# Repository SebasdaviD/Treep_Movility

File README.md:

# Treep_Movility
Por Sebastian David Mazo Cadavid (sebastiandavidmazo@gmail.com) 

Repositorio para el código correspondiente a el desarrollo de la programación de los diferentes sistemas electrónicos de una moto eléctrica.

////////////////////////////                          Etapa de sensórica:                           /////////////////////////////////////////////////

La finalidad de esta etapa es describir de forma dínamica el comportamiento de la moto eléctrica, por lo que se van a medir las siguientes variables:

- Aceleraciones
- Giros
- Campo magnético
- Voltaje
- Corriente
- Potencia de electrónica
- Desplazamientos
- Ubicación global
- Velocidad angular

Para medir dichas variables se hace uso de la siguiente lista de dispositivos:

- Tarjeta de desarrollo WIDORA AIR V6.0

- Sensor MPU-9255 (DOF-IMU) 
    Medición de aceleraciones giros y campos magnéticos
    
- Multiplexor TCA9548A
    Usado para conectar varios dispositivos MPU-9255 de manera simultanea

- Módulo sensor de Efecto Hall 3144 5v
    Medición de velocidad
    
- Módulo de distancia Adafruit VL53L0X
    Usado para medir la distancia de desplazamiento de los amortiguadores

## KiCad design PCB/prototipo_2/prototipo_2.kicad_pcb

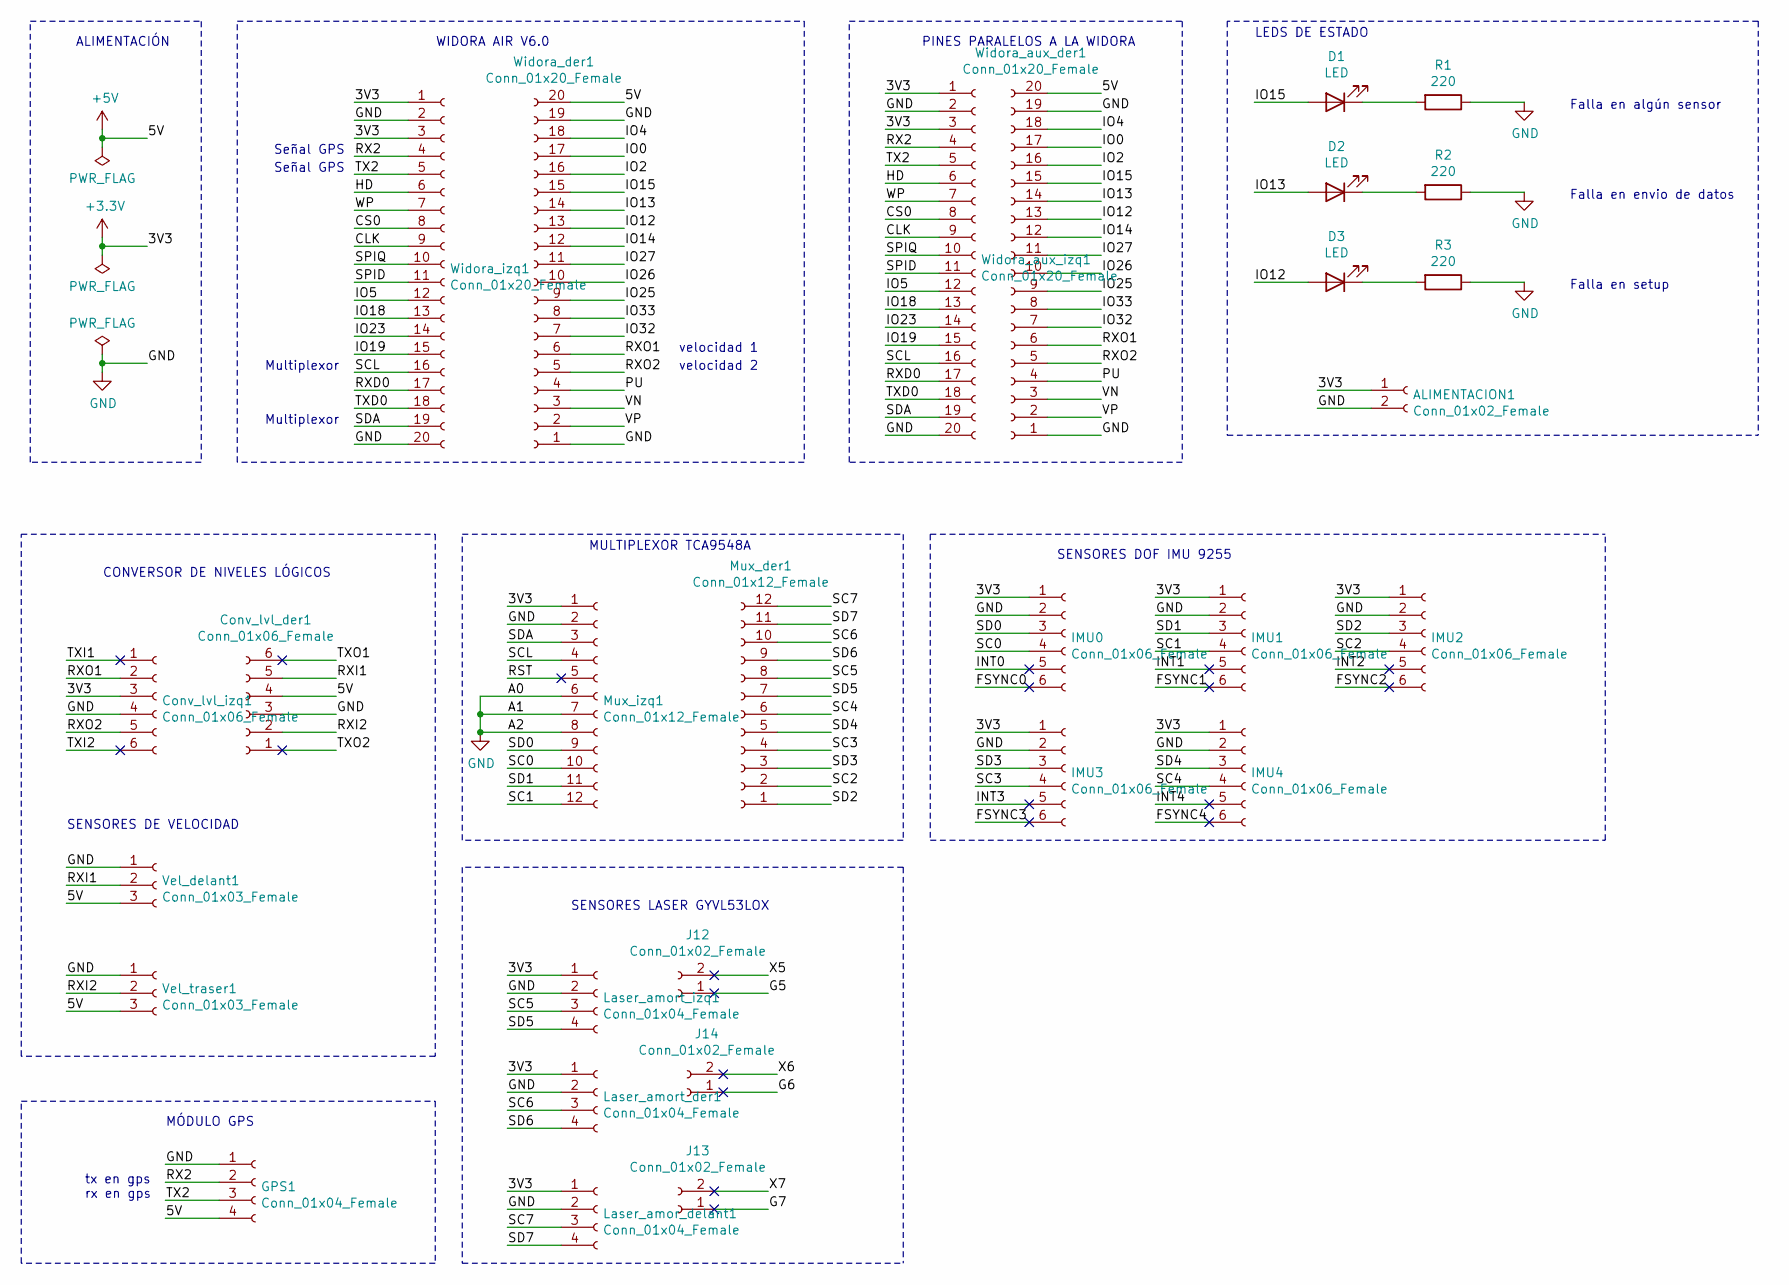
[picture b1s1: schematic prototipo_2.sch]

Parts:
ALIMENTACION1: Conn_01x02_Female; PinSocket_1x02_P2.54mm_Vertical
Conv_lvl_der1: Conn_01x06_Female; PinSocket_1x06_P2.54mm_Vertical
Conv_lvl_izq1: Conn_01x06_Female; PinSocket_1x06_P2.54mm_Vertical
D1, D2, D3: LED; LED_D5.0mm
GPS1: Conn_01x04_Female; PinSocket_1x04_P2.54mm_Vertical
IMU0, IMU1, IMU2, IMU3, IMU4: Conn_01x06_Female; PinSocket_1x06_P2.54mm_Vertical
J12, J13, J14: Conn_01x02_Female; PinSocket_1x02_P2.54mm_Vertical
Laser_amor_delant1: Conn_01x04_Female; PinSocket_1x04_P2.54mm_Vertical
Laser_amort_der1: Conn_01x04_Female; PinSocket_1x04_P2.54mm_Vertical
Laser_amort_izq1: Conn_01x04_Female; PinSocket_1x04_P2.54mm_Vertical
Mux_der1: Conn_01x12_Female; PinSocket_1x12_P2.54mm_Vertical
Mux_izq1: Conn_01x12_Female; PinSocket_1x12_P2.54mm_Vertical
R1, R2, R3: 220; R_Axial_DIN0411_L9.9mm_D3.6mm_P12.70mm_Horizontal
Vel_delant1: Conn_01x03_Female; PinSocket_1x03_P2.54mm_Vertical
Vel_traser1: Conn_01x03_Female; PinSocket_1x03_P2.54mm_Vertical
Widora_aux_der1: Conn_01x20_Female; PinSocket_1x20_P2.54mm_Vertical
Widora_aux_izq1: Conn_01x20_Female; PinSocket_1x20_P2.54mm_Vertical
Widora_der1: Conn_01x20_Female; PinSocket_1x20_P2.54mm_Vertical
Widora_izq1: Conn_01x20_Female; PinSocket_1x20_P2.54mm_Vertical

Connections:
+3V3: ALIMENTACION1.1, Conv_lvl_izq1.3, IMU0.1, IMU1.1, IMU2.1, IMU3.1, IMU4.1, Laser_amor_delant1.1, Laser_amort_der1.1, Laser_amort_izq1.1, Mux_izq1.1, Widora_aux_izq1.1, Widora_aux_izq1.3, Widora_izq1.1, Widora_izq1.3
+5V: Conv_lvl_der1.4, GPS1.4, Vel_delant1.3, Vel_traser1.3, Widora_aux_der1.20, Widora_der1.20
/CLK: Widora_aux_izq1.9, Widora_izq1.9
/CS0: Widora_aux_izq1.8, Widora_izq1.8
/FSYNC0: IMU0.6
/FSYNC1: IMU1.6
/FSYNC2: IMU2.6
/FSYNC3: IMU3.6
/FSYNC4: IMU4.6
/G5: J12.1
/G6: J14.1
/G7: J13.1
/HD: Widora_aux_izq1.6, Widora_izq1.6
/INT0: IMU0.5
/INT1: IMU1.5
/INT2: IMU2.5
/INT3: IMU3.5
/INT4: IMU4.5
/IO0: Widora_aux_der1.17, Widora_der1.17
/IO2: Widora_aux_der1.16, Widora_der1.16
/IO4: Widora_aux_der1.18, Widora_der1.18
/IO5: Widora_aux_izq1.12, Widora_izq1.12
/IO12: D3.2 (A), Widora_aux_der1.13, Widora_der1.13
/IO13: D2.2 (A), Widora_aux_der1.14, Widora_der1.14
/IO14: Widora_aux_der1.12, Widora_der1.12
/IO15: D1.2 (A), Widora_aux_der1.15, Widora_der1.15
/IO18: Widora_aux_izq1.13, Widora_izq1.13
/IO19: Widora_aux_izq1.15, Widora_izq1.15
/IO23: Widora_aux_izq1.14, Widora_izq1.14
/IO25: Widora_aux_der1.9, Widora_der1.9
/IO26: Widora_aux_der1.10, Widora_der1.10
/IO27: Widora_aux_der1.11, Widora_der1.11
/IO32: Widora_aux_der1.7, Widora_der1.7
/IO33: Widora_aux_der1.8, Widora_der1.8
/PU: Widora_aux_der1.4, Widora_der1.4
/RST: Mux_izq1.5
/RX2: GPS1.2, Widora_aux_izq1.4, Widora_izq1.4
/RXD0: Widora_aux_izq1.17, Widora_izq1.17
/RXI1: Conv_lvl_der1.5, Vel_delant1.2
/RXI2: Conv_lvl_der1.2, Vel_traser1.2
/RXO1: Conv_lvl_izq1.2, Widora_aux_der1.6, Widora_der1.6
/RXO2: Conv_lvl_izq1.5, Widora_aux_der1.5, Widora_der1.5
/SC0: IMU0.4, Mux_izq1.10
/SC1: IMU1.4, Mux_izq1.12
/SC2: IMU2.4, Mux_der1.2
/SC3: IMU3.4, Mux_der1.4
/SC4: IMU4.4, Mux_der1.6
/SC5: Laser_amort_izq1.3, Mux_der1.8
/SC6: Laser_amort_der1.3, Mux_der1.10
/SC7: Laser_amor_delant1.3, Mux_der1.12
/SCL: Mux_izq1.4, Widora_aux_izq1.16, Widora_izq1.16
/SD0: IMU0.3, Mux_izq1.9
/SD1: IMU1.3, Mux_izq1.11
/SD2: IMU2.3, Mux_der1.1
/SD3: IMU3.3, Mux_der1.3
/SD4: IMU4.3, Mux_der1.5
/SD5: Laser_amort_izq1.4, Mux_der1.7
/SD6: Laser_amort_der1.4, Mux_der1.9
/SD7: Laser_amor_delant1.4, Mux_der1.11
/SDA: Mux_izq1.3, Widora_aux_izq1.19, Widora_izq1.19
/SPID: Widora_aux_izq1.11, Widora_izq1.11
/SPIQ: Widora_aux_izq1.10, Widora_izq1.10
/TX2: GPS1.3, Widora_aux_izq1.5, Widora_izq1.5
/TXD0: Widora_aux_izq1.18, Widora_izq1.18
/TXI1: Conv_lvl_izq1.1
/TXI2: Conv_lvl_izq1.6
/TXO1: Conv_lvl_der1.6
/TXO2: Conv_lvl_der1.1
/VN: Widora_aux_der1.3, Widora_der1.3
/VP: Widora_aux_der1.2, Widora_der1.2
/WP: Widora_aux_izq1.7, Widora_izq1.7
/X5: J12.2
/X6: J14.2
/X7: J13.2
GND: ALIMENTACION1.2, Conv_lvl_der1.3, Conv_lvl_izq1.4, GPS1.1, IMU0.2, IMU1.2, IMU2.2, IMU3.2, IMU4.2, Laser_amor_delant1.2, Laser_amort_der1.2, Laser_amort_izq1.2, Mux_izq1.2, Mux_izq1.6, Mux_izq1.7, Mux_izq1.8, R1.1, R2.1, R3.1, Vel_delant1.1, Vel_traser1.1, Widora_aux_der1.1, Widora_aux_der1.19, Widora_aux_izq1.2, Widora_aux_izq1.20, Widora_der1.1, Widora_der1.19, Widora_izq1.2, Widora_izq1.20
unnamed: D1.1 (K), R1.2
unnamed: D2.1 (K), R2.2
unnamed: D3.1 (K), R3.2

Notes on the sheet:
SENSORES DOF IMU 9255
SENSORES LASER GYVL53LOX
SENSORES DE VELOCIDAD
CONVERSOR DE NIVELES LÓGICOS
tx en gps rx en gps
MÓDULO GPS
WIDORA AIR V6.0
velocidad 1
velocidad 2
Señal GPS
Multiplexor
PINES PARALELOS A LA WIDORA
Falla en algún sensor
Falla en envio de datos
Falla en setup
LEDS DE ESTADO
MULTIPLEXOR TCA9548A
ALIMENTACIÓN

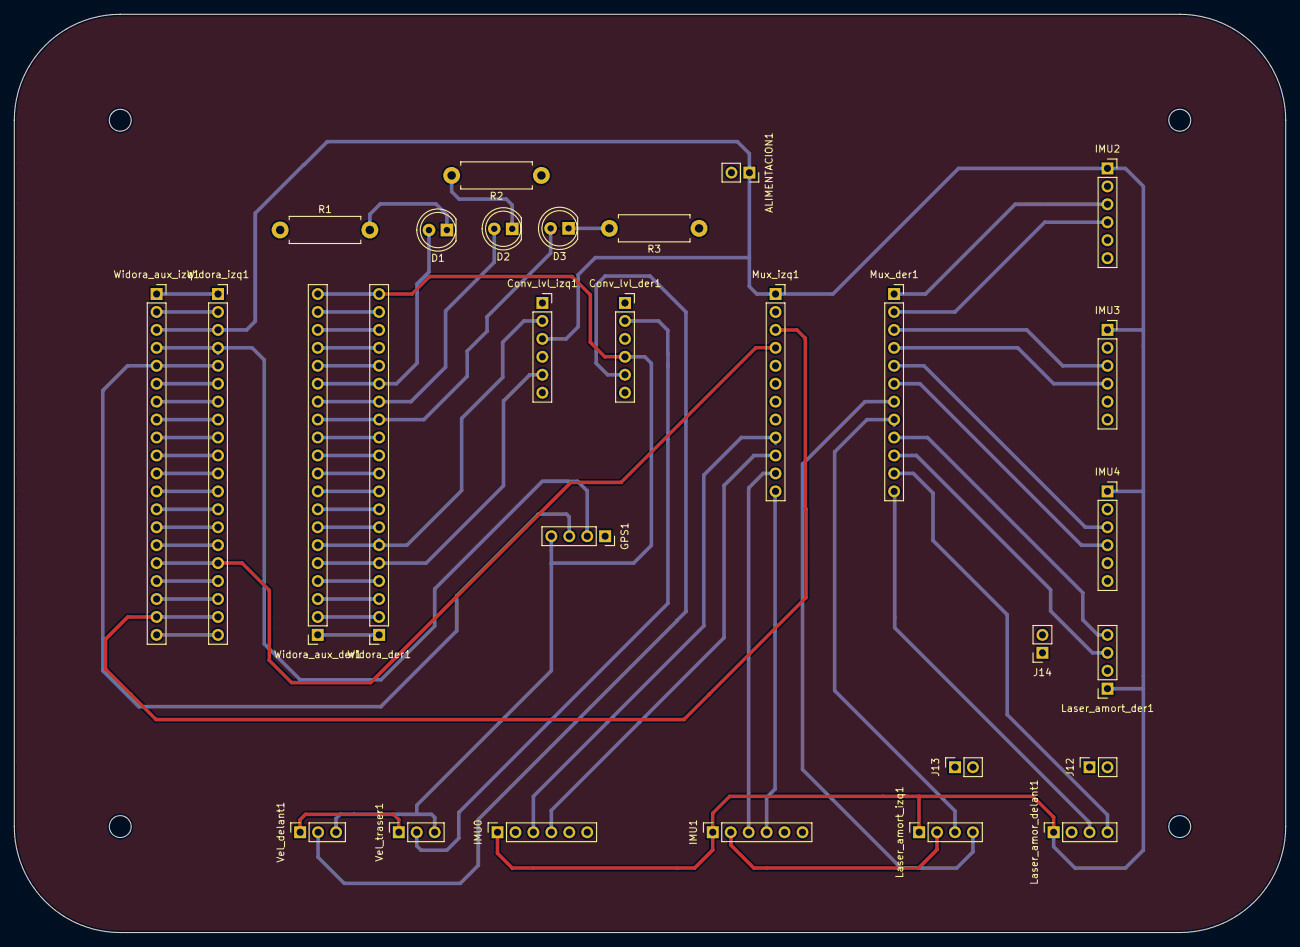
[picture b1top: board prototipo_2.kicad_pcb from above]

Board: 2 copper layers, 180.0 x 130.0 mm, 29 parts (0 on the bottom side), 57 nets.

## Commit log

2021-06-13 Primera version del proyecto
2021-06-16 Se agrega código de sensor de velocidad en dos ńucleos
2021-06-16 Actualización de documento oficial e informe
2021-10-01 Se agrega al codigo principal la medicion de distancia
2021-10-23 Agregado al codigo principal el modulo de lectura SD con sus respectivas librerias
2021-10-27 Agregado una nueva forma de medir la velocidad, pero al pasar al microcontrolador principal se reinicio, probablemente se deba usar el conversor de niveles logicos, dicho codigo fue agregado tambien 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
